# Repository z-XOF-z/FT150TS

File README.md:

<div align="center">

<br/>

**El tablero que la FT150TS no traía de fábrica.**

Tablero digital + launcher para Android que funciona **solo con el teléfono** del manubrio
y está listo para una tarjeta **ESP32** en la moto.

[![Android][android-shield]](#empezar)
[![Kotlin][kotlin-shield]](app/src/main/java/com/xof/ft150ts)
[![Jetpack Compose][compose-shield]](app/src/main/java/com/xof/ft150ts/ui)
[![ESP32-S3][esp32-shield]](firmware/ft150ts_dashboard)
[![Versión][version-shield]](LEEME.md)

### [⬇ Descargar la app (APK v3.4 estable)](https://github.com/z-XOF-z/FT150TS/releases/latest)

**[Qué hace](#qué-hace)** · **[Empezar](#empezar)** · **[La tarjeta ESP32](#la-tarjeta-esp32)** · **[Historial completo](LEEME.md)**

</div>

---

## Por qué

El teléfono ya iba en el manubrio de la moto. En vez de solo mirar el mapa, se vuelve el **tablero completo**:
velocidad, RPM, marcha, inclinación, mantenimiento, gasolina y navegación, con un diseño pixel y deportivo
pensado para la FT150TS. Sin cables extra: las RPM salen de la **vibración del motor** que siente el teléfono.
Cuando llegue la tarjeta ESP32, ella manda los datos que el teléfono no puede medir (voltaje, temperatura, RPM
directas) y la app se cambia sola.

## Qué hace

<div align="center">

</div>

| Capacidad | Qué te da |
| --- | --- |
| **Tablero LCD Sport** | Barra de RPM curva o diagonal a 45°, dígitos de 7 segmentos, marcha, shift light y animación de arranque (las RPM suben al tope y regresan, como al dar switch). |
| **RPM sin sensor** | La vibración del motor por FFT de 3 ejes, peine de armónicos y filtro de Kalman. Se calibra en 6 s en ralentí. |
| **Marcha** | Velocidad + RPM + la marcha anterior en un filtro de probabilidad: no marca "4ª a 17 km/h". |
| **Aguja con PID** | La aguja tiene inercia de verdad; Kp, Ki y Kd ajustables con gráfica de respuesta. |
| **Mapa** | OpenStreetMap que gira suave con la brújula, satélites y doble frecuencia L5, dónde dejé la moto, límite de velocidad, "llévame a casa". |
| **Modo moto** | El cable de la moto hace de switch: carga = tablero, sin carga = tus apps. Etiqueta NFC del soporte y **modo sueño** cuando carga sin moverse. |
| **Launcher** | Pantalla de inicio con tus apps, 4 accesos directos y tres estilos de íconos (normales, pixel, LCD). |
| **Rodadas** | Cada rodada se graba sola; mírala en el mapa pintado por velocidad y **repítela** x10/x30/x60. Aviso de descanso. |
| **Arrancones** | 0-40/60/80, 100 m y 1/8 de milla con semáforo y tiempo de reacción, y prueba de frenado 40→0 (en lugar cerrado). |
| **Lluvia en tu ruta** | Revisa el pronóstico kilómetros adelante en la dirección en que vas y te avisa antes de mojarte. |
| **Velocímetro vs GPS** | Cuánto marca de más tu velocímetro y a cuánto vas de verdad. |
| **Mantenimiento** | Odómetro del teléfono, servicios por km, bitácora de gasolina con rendimiento y **alcance**. |
| **Respaldo** | Todos tus datos en un archivo: guárdalo, compártelo o deja el automático semanal. |
| **Seguridad** | Dashcam en bucle que guarda el video si detecta un golpe, aviso de teléfono caliente, batería del cel. |
| **Clima y alertas** | Lluvia próxima, huracanes (NHC), sismos (USGS) y clima severo en el tablero. |
| **Temas** | **Vértice** (riel lateral, nuevo), Carbono, Vidrio, Filo, Pixel, Táctico, Holo, Ácido y Circuito · efecto neón · 18 colores + uno personalizado · 4 fondos. |
| **Reposo** | Moto parada y cargando: reloj atenuado o pantalla apagada, GPS en pausa; despierta solo al dar marcha. |

### La idea en una línea

> El teléfono que ya va en el manubrio se vuelve el tablero; la ESP32 le da lo que el teléfono no puede medir.

## Empezar

### 1. Instala la app

**La rápida:** descarga el APK del [último release](https://github.com/z-XOF-z/FT150TS/releases/latest) en tu
teléfono (Android 8.0 o más nuevo), ábrelo y permite "Instalar apps desconocidas".

**Actualizar:** desde la 3.2-beta.1, en la app: Ajustes → Acerca de → **Buscar actualización** (prende "Versiones de prueba" para recibir betas). Se instala encima sin
borrar tus datos. Detalles y cómo publicar una versión en [docs/RELEASE.md](docs/RELEASE.md).

**Desde el código:**

Abre esta carpeta en **Android Studio**, conecta el teléfono (depuración USB) y:

```bash
./gradlew installDebug      # normal
./gradlew installRelease    # optimizada, más fluida (misma firma: no borra tus datos)
```

Requiere Android 8.0 o más nuevo. Siempre se instala **encima**: tu odómetro, marchas aprendidas y ajustes se quedan.

### 2. Calibra las RPM (una vez)

Moto en neutral, motor caliente en ralentí y el teléfono en el soporte:
**Ajustes > Sin la tarjeta > Calibrar en ralentí** (6 segundos).

### 3. Escoge tu estilo

**Ajustes > Apariencia**: tema, color de acento, neón, fondo, forma de la barra de RPM y la animación de entrada.

## La tarjeta ESP32

Firmware en [`firmware/ft150ts_dashboard`](firmware/ft150ts_dashboard), placa **ESP32-S3**, particiones *Huge APP*:

```bash
arduino-cli compile --fqbn espressif:esp32:esp32s3:PartitionScheme=huge_app firmware/ft150ts_dashboard
```

Desde la v1.4 cada tarjeta genera su propia clave de WiFi (se ve por USB al encender o con `wifi clave`) y los
comandos delicados solo se aceptan de un teléfono vinculado. Detalles en [SEGURIDAD.md](SEGURIDAD.md).

## Placa base y piezas 3D

- **Placa base v2.3** para el ESP32-S3 N16R8 (10×10 cm, 2 capas, piezas de agujero de tiendas de México): guía de armado y conexiones a la moto en [`pcb/ARMADO.md`](pcb/ARMADO.md), esquemático en [PDF](pcb/esquematico/ft150ts_B_esquema.pdf), gerbers para JLCPCB en [`pcb/fabricar/B_JLCPCB`](pcb/fabricar/B_JLCPCB) y piezas en [`pcb/LISTA_COMPRAS.md`](pcb/LISTA_COMPRAS.md).
- **Placas extra** (expansión I2C con 3 relevadores, fusibles y perforada): [`pcb/extras`](pcb/extras).
- **Simulaciones** de cada bloque (ngspice/KiCad): [`pcb/simulacion`](pcb/simulacion).
- **Piezas 3D** (CadQuery): soporte del teléfono para el manubrio y caja de la placa bajo el asiento, en [`carcasa`](carcasa) (STL y STEP).
- Mapa de todo el proyecto: [`docs/MAPA.md`](docs/MAPA.md).

## Temas

<div align="center">

<br/><sub>Tema Filo: barra integrada con segmentos a 45° y todo dentro de un marco tipo visor.</sub>
</div>

## Hoja de ruta

- [x] Tablero LCD Sport y Clásico con aguja PID
- [x] RPM por vibración, marcha por velocidad + RPM
- [x] Modo moto, NFC, modo sueño
- [x] Temas Filo, Pixel y Táctico, neón y colores personalizados
- [x] Respaldo y restaurar todos tus datos en un archivo
- [x] Modo arrancones (0–60 km/h, 1/8 de milla, semáforo) y prueba de frenado
- [x] Lluvia en tu ruta
- [x] Repetición de rodadas coloreada por velocidad
- [x] Error del velocímetro contra el GPS
- [x] Logros pixel (y un secreto)
- [x] Tema Vértice, modo reposo y medidor de fluidez
- [x] Auditoría de seguridad (WiFi y Bluetooth de la tarjeta, respaldo)
- [ ] Antirrobo (con la ESP32)
- [ ] Temperatura del motor, nivel de gasolina real y presión de llantas (con la ESP32)

## Estructura

```
app/                      App de Android (Kotlin + Jetpack Compose)
  src/main/java/com/xof/ft150ts/
    ui/                   Pantallas, temas, barra integrada, animaciones
    *.kt                  GPS, sensores, RPM, marcha, modo moto, modo sueño...
firmware/
  ft150ts_dashboard/      Firmware del ESP32-S3 (Arduino)
docs/                     Banner animado, GIFs e imágenes
releases/                 APK listo para instalar y notas de cada versión
LEEME.md                  Guía completa e historial de versiones
```

---

<div align="center">

Hecho por **XOF** para su Italika FT150TS.

<sub>Tipografías Chakra Petch, Russo One y Press Start 2P con licencia OFL ([LICENCIAS_FUENTES.txt](LICENCIAS_FUENTES.txt)) · Mapas © colaboradores de OpenStreetMap</sub>

</div>

[android-shield]: https://img.shields.io/badge/Android-8.0%2B-9BE22B?style=for-the-badge&logo=android&logoColor=white&labelColor=0E1113
[kotlin-shield]: https://img.shields.io/badge/Kotlin-2.1-9BE22B?style=for-the-badge&logo=kotlin&logoColor=white&labelColor=0E1113
[compose-shield]: https://img.shields.io/badge/Jetpack%20Compose-Material%203-9BE22B?style=for-the-badge&logo=jetpackcompose&logoColor=white&labelColor=0E1113
[esp32-shield]: https://img.shields.io/badge/ESP32--S3-firmware-9BE22B?style=for-the-badge&logo=espressif&logoColor=white&labelColor=0E1113
[version-shield]: https://img.shields.io/badge/versi%C3%B3n-3.4-9BE22B?style=for-the-badge&labelColor=0E1113

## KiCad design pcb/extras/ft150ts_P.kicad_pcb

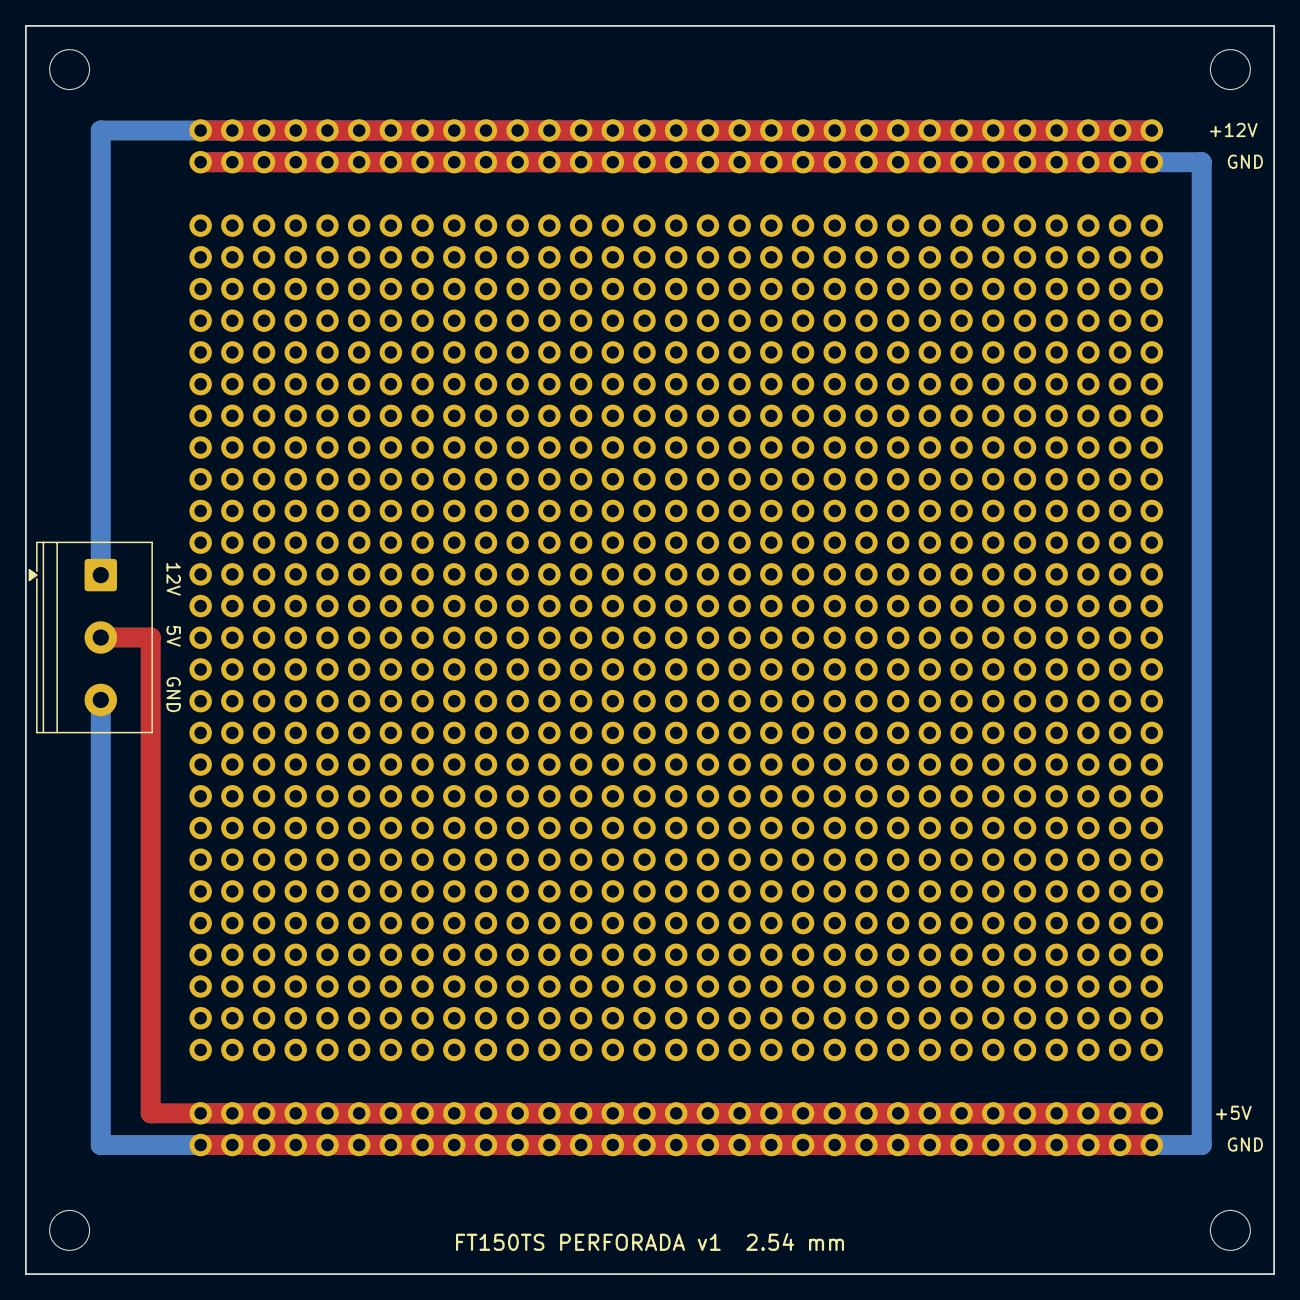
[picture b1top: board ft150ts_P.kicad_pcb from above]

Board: 2 copper layers, 100.0 x 100.0 mm, 6 parts (0 on the bottom side), 3 nets.

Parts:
H1, H2, H3, H4: MountingHole_3.2mm_M3
J1: TerminalBlock_Phoenix_PT-1,5-3-5.0-H_1x03_P5.00mm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; TerminalBlock_Phoenix_PT-1,5-3-5.0-H_1x03_P5.00mm_Horizontal
PERF: (no value)

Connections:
+5V: J1.2, PERF.30, PERF.61, PERF.92, PERF.123, PERF.154, PERF.185, PERF.216, PERF.247, PERF.278, PERF.309, PERF.340, PERF.371, PERF.402, PERF.433, PERF.464, PERF.495, PERF.526, PERF.557, PERF.588, PERF.619, PERF.650, PERF.681, PERF.712, PERF.743, PERF.774, PERF.805, PERF.836, PERF.867, PERF.898, PERF.929, PERF.960
+12V: J1.1, PERF.28, PERF.59, PERF.90, PERF.121, PERF.152, PERF.183, PERF.214, PERF.245, PERF.276, PERF.307, PERF.338, PERF.369, PERF.400, PERF.431, PERF.462, PERF.493, PERF.524, PERF.555, PERF.586, PERF.617, PERF.648, PERF.679, PERF.710, PERF.741, PERF.772, PERF.803, PERF.834, PERF.865, PERF.896, PERF.927, PERF.958
GND: J1.3, PERF.29, PERF.31, PERF.60, PERF.62, PERF.91, PERF.93, PERF.122, PERF.124, PERF.153, PERF.155, PERF.184, PERF.186, PERF.215, PERF.217, PERF.246, PERF.248, PERF.277, PERF.279, PERF.308, PERF.310, PERF.339, PERF.341, PERF.370, PERF.372, PERF.401, PERF.403, PERF.432, PERF.434, PERF.463, PERF.465, PERF.494, PERF.496, PERF.525, PERF.527, PERF.556, PERF.558, PERF.587, PERF.589, PERF.618, PERF.620, PERF.649, PERF.651, PERF.680, PERF.682, PERF.711, PERF.713, PERF.742, PERF.744, PERF.773, PERF.775, PERF.804, PERF.806, PERF.835, PERF.837, PERF.866, PERF.868, PERF.897, PERF.899, PERF.928, PERF.930, PERF.959, PERF.961

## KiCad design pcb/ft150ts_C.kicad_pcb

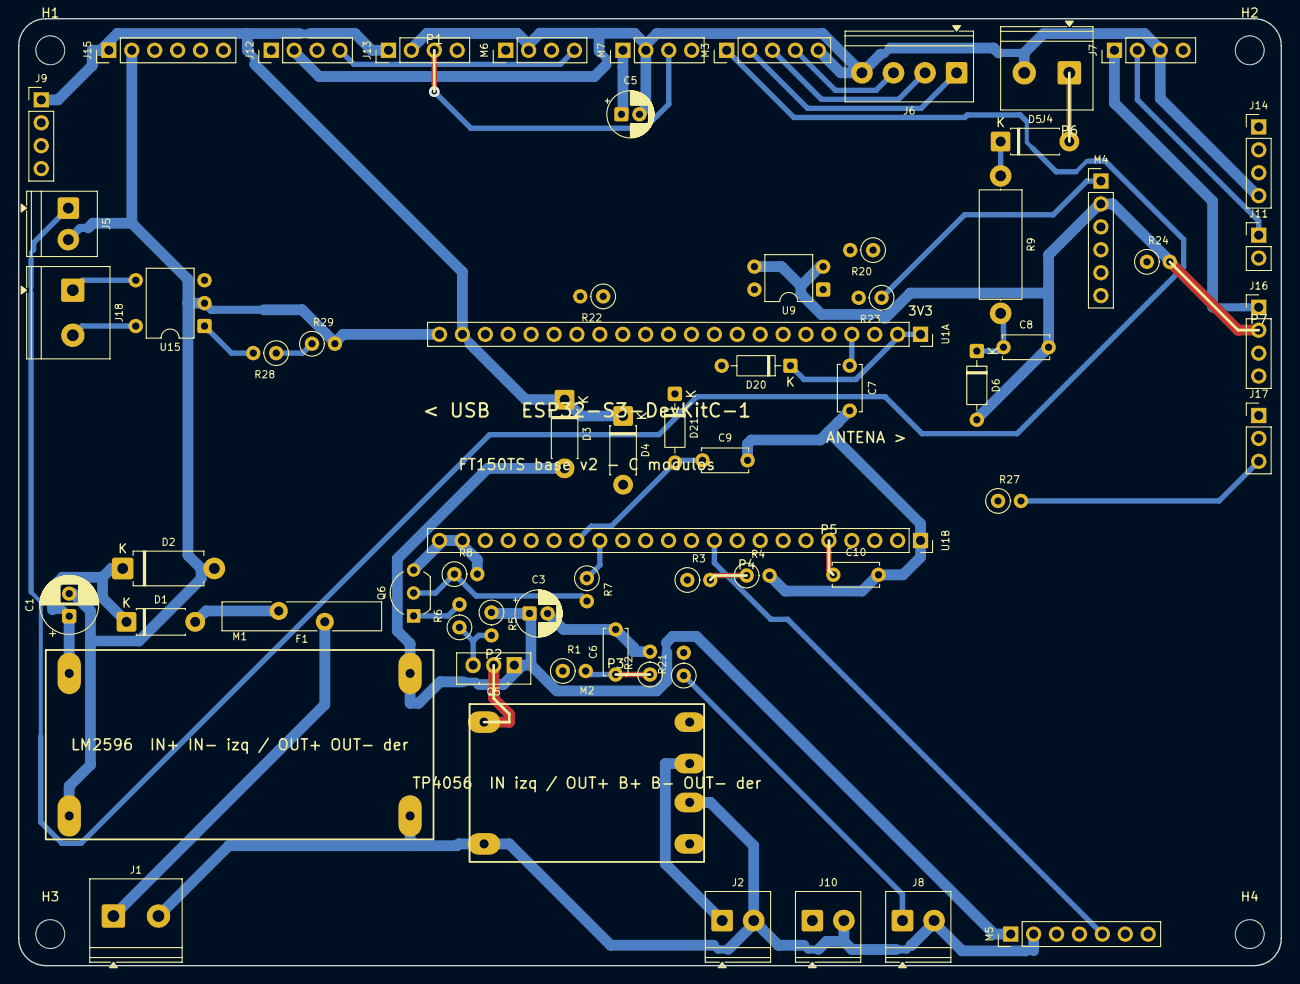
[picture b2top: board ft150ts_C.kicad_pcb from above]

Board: 2 copper layers, 140.0 x 105.0 mm, 68 parts (0 on the bottom side), 57 nets.

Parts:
C1: 100uF 35V; CP_Radial_D6.3mm_P2.50mm
C3, C5: 100uF 10V; CP_Radial_D5.0mm_P2.00mm
C6, C7, C9, C10: 100nF; C_Disc_D5.0mm_W2.5mm_P5.00mm
C8: 4.7nF; C_Disc_D5.0mm_W2.5mm_P5.00mm
D1, D3, D4: 1N5819; D_DO-41_SOD81_P7.62mm_Horizontal
D2: P6KE22A; D_DO-15_P10.16mm_Horizontal
D5: 1N4007; D_DO-41_SOD81_P7.62mm_Horizontal
D6: 1N4148; D_DO-35_SOD27_P7.62mm_Horizontal
D20, D21: BAT85; D_DO-35_SOD27_P7.62mm_Horizontal
F1: MF-R110 1.1A; Fuse_Bourns_MF-RG1100
H1, H2, H3, H4: MountingHole_3.2mm_M3
J1: BAT MOTO 12V; TerminalBlock_Phoenix_PT-1,5-2-5.0-H_1x02_P5.00mm_Horizontal
J2: BATERIA 3.7V; TerminalBlock_Phoenix_PT-1,5-2-3.5-H_1x02_P3.50mm_Horizontal
J4: BOBINA; TerminalBlock_Phoenix_PT-1,5-2-5.0-H_1x02_P5.00mm_Horizontal
J5: LLAVE; TerminalBlock_Phoenix_PT-1,5-2-3.5-H_1x02_P3.50mm_Horizontal
J6: ENTRADAS 3-16V; TerminalBlock_Phoenix_PT-1,5-4-3.5-H_1x04_P3.50mm_Horizontal
J7: HALL; PinHeader_1x04_P2.54mm_Vertical
J8: QUICKSHIFT; TerminalBlock_Phoenix_PT-1,5-2-3.5-H_1x02_P3.50mm_Horizontal
J9: DS18B20; PinHeader_1x04_P2.54mm_Vertical
J10: GASOLINA; TerminalBlock_Phoenix_PT-1,5-2-3.5-H_1x02_P3.50mm_Horizontal
J11: LDR; PinHeader_1x02_P2.54mm_Vertical
J12: I2C 3V3; PinHeader_1x04_P2.54mm_Vertical
J13: LCD 5V; PinHeader_1x04_P2.54mm_Vertical
J14: BOTONES; PinHeader_1x04_P2.54mm_Vertical
J15: SD; PinHeader_1x06_P2.54mm_Vertical
J16: GPS; PinHeader_1x04_P2.54mm_Vertical
J17: LEDS; PinHeader_1x03_P2.54mm_Vertical
J18: CDI PARO; TerminalBlock_Phoenix_PT-1,5-2-5.0-H_1x02_P5.00mm_Horizontal
M1: LM2596; Modulo_LM2596_43x21
M2: TP4056; Modulo_TP4056_26x17
M3: OPTO 4CH ENTRADA; PinHeader_1x05_P2.54mm_Vertical
M4: OPTO 4CH SALIDA; PinHeader_1x06_P2.54mm_Vertical
M5: RELES 4CH; PinHeader_1x07_P2.54mm_Vertical
M6: NIVEL LV; PinHeader_1x04_P2.54mm_Vertical
M7: NIVEL HV; PinHeader_1x04_P2.54mm_Vertical
Q5: BD140; TO-126-3_Vertical
Q6: BC547; TO-92_Inline_Wide
R1, R3, R4: 100k; R_Axial_DIN0207_L6.3mm_D2.5mm_P2.54mm_Vertical
R2: 22k; R_Axial_DIN0207_L6.3mm_D2.5mm_P2.54mm_Vertical
R5, R7, R23: 1k; R_Axial_DIN0207_L6.3mm_D2.5mm_P2.54mm_Vertical
R6: 150; R_Axial_DIN0207_L6.3mm_D2.5mm_P2.54mm_Vertical
R8, R24, R29: 10k; R_Axial_DIN0207_L6.3mm_D2.5mm_P2.54mm_Vertical
R9: 47k 1W; R_Axial_DIN0414_L11.9mm_D4.5mm_P15.24mm_Horizontal
R20, R21: 2.2k; R_Axial_DIN0207_L6.3mm_D2.5mm_P2.54mm_Vertical
R22: 4.7k; R_Axial_DIN0207_L6.3mm_D2.5mm_P2.54mm_Vertical
R27, R28: 330; R_Axial_DIN0207_L6.3mm_D2.5mm_P2.54mm_Vertical
U1A: DevKitC-1 J1; PinSocket_1x22_P2.54mm_Vertical
U1B: DevKitC-1 J3; PinSocket_1x22_P2.54mm_Vertical
U9: PC817; DIP-4_W7.62mm
U15: PhotoMOS 600V; DIP-6_W7.62mm_SinPin5

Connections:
+3V3: D20.1, D21.1, J7.2, J9.2, J11.1, J12.1, M4.1, M5.3, M6.1, R22.1, R23.1, U1A.1, U1A.2
+5V: C5.1, D3.1, D4.1, J7.1, J9.1, J13.1, J15.1, J16.1, J17.1, M7.1, U1A.21
+5V_MOTO: C3.1, D3.2, M1.3, M5.1, Q5.1, R5.1
+12V: C1.1, D1.1, D2.1, M1.1
+12V_F: D1.2, F1.2
+12V_IN: F1.1, J1.1, R1.1
BOBINA: D5.2, J4.1
CARGA5: M2.1, Q5.2
CARGA_B: Q6.2, R7.2, R8.1
CARGA_BP: Q5.3, R5.2, R6.1
CARGA_C: Q6.1, R6.2
CDI_PARO: J18.1, U15.4
CDI_TIERRA: J18.2, U15.6
CELDA: D4.2, J2.1, M2.3, R3.1
ENT1: J6.1, M3.2
ENT2: J6.2, M3.3
ENT3: J6.3, M3.4
GND: C1.2, C3.2, C5.2, C6.2, C7.2, C8.2, C9.2, C10.2, D2.2, D6.2, J1.2, J2.2, J4.2, J5.2, J6.4, J7.3, J8.2, J9.3, J10.2, J12.2, J13.2, J14.4, J15.2, J16.2, J17.2, M1.2, M1.4, M2.2, M2.4, M3.5, M4.2, M5.2, M6.2, M7.2, Q6.3, R2.2, R4.2, R8.2, R24.2, R29.2, U1A.22, U1B.1, U1B.21, U1B.22, U9.2, U9.3, U15.2
IO1: C6.1, R1.2, R2.1, U1B.4
IO2: C10.1, J10.1, R23.2, U1B.5
IO3: M4.5, U1A.13
IO4: C7.1, R3.2, R4.1, U1A.4
IO5: J11.2, R24.1, U1A.5
IO6: J14.1, U1A.6
IO7: J14.2, U1A.7
IO8: J12.3, M6.3, U1A.12
IO9: J12.4, M6.4, U1A.15
IO10: J15.3, U1A.16
IO11: J15.4, U1A.17
IO12: J15.5, U1A.18
IO13: J15.6, U1A.19
IO14: J9.4, R22.2, U1A.20
IO15: J14.3, U1A.8
IO16: U1A.9, U9.4
IO17: D20.2, R20.2, U1A.10
IO18: M4.4, U1A.11
IO21: M4.3, U1B.18
IO38: M5.5, U1B.10
IO39: R27.1, U1B.9
IO40: M5.4, U1B.8
IO41: J16.3, U1B.7
IO42: J16.4, U1B.6
IO43: M5.7, U1B.2
IO44: M5.6, U1B.3
IO45: R7.1, U1B.15
IO46: M4.6, U1A.14
IO47: R28.1, R29.1, U1B.17
IO48: C9.1, D21.2, R21.2, U1B.16
LED_DIN: J17.3, R27.2
LLAVE: J5.1, M3.1
OPT9_A: C8.1, D6.1, R9.2, U9.1
RPM_A: D5.1, R9.1
S20: J7.4, R20.1
S21: J8.1, R21.1
SCL5: J13.4, M7.4
SDA5: J13.3, M7.3
SSR_A: R28.2, U15.1

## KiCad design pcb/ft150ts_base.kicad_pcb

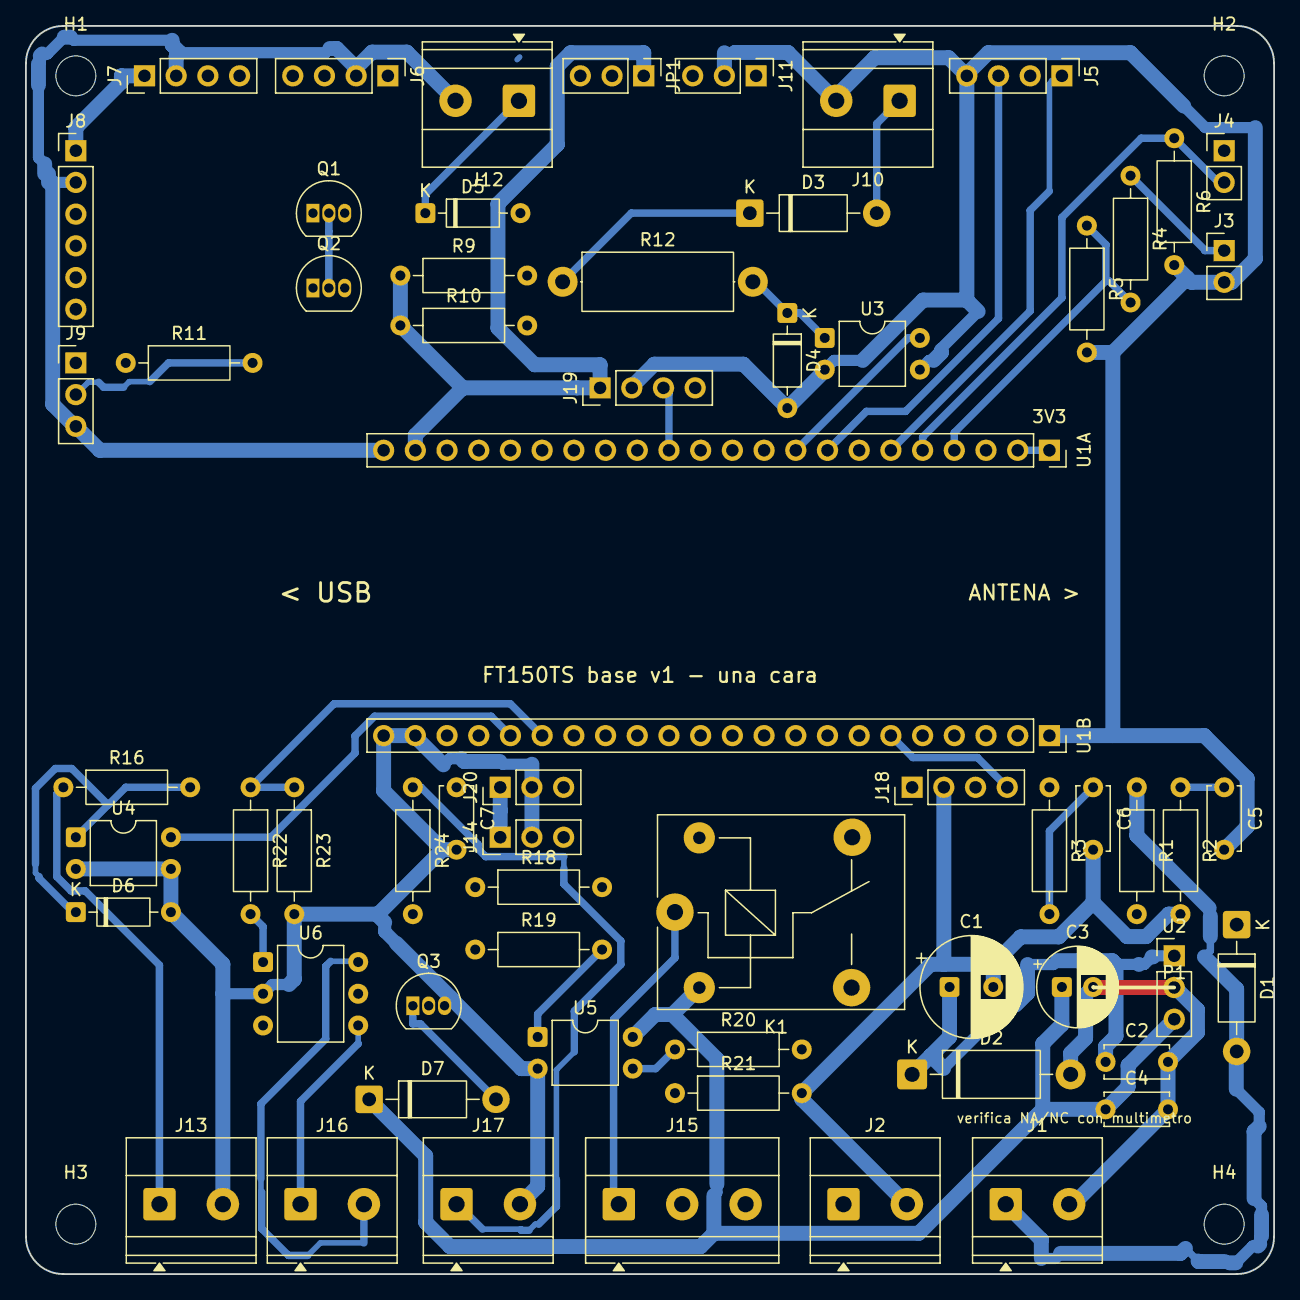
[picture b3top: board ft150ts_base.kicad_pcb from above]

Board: 2 copper layers, 100.0 x 100.0 mm, 68 parts (0 on the bottom side), 54 nets.

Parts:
C1: 100uF 35V; CP_Radial_D8.0mm_P3.50mm
C2, C4, C5, C6, C7: 100nF; C_Disc_D5.0mm_W2.5mm_P5.00mm
C3: 100uF 10V; CP_Radial_D6.3mm_P2.50mm
D1: 1N5819; D_DO-41_SOD81_P10.16mm_Horizontal
D2: P6KE24A; D_DO-15_P12.70mm_Horizontal
D3, D7: 1N4007; D_DO-41_SOD81_P10.16mm_Horizontal
D4, D5, D6: 1N4148; D_DO-35_SOD27_P7.62mm_Horizontal
H1, H2, H3, H4: MountingHole_3.2mm_M3
J1: 12V MOTO; TerminalBlock_Phoenix_MKDS-1,5-2-5.08_1x02_P5.08mm_Horizont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
J2: GASOLINA; TerminalBlock_Phoenix_MKDS-1,5-2-5.08_1x02_P5.08mm_Horizont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
J3: 18650; PinHeader_1x02_P2.54mm_Vertical
J4: LDR; PinHeader_1x02_P2.54mm_Vertical
J5: BOTONES; PinHeader_1x04_P2.54mm_Vertical
J6: I2C 3V3; PinHeader_1x04_P2.54mm_Vertical
J7: LCD 5V; PinHeader_1x04_P2.54mm_Vertical
J8: SD; PinHeader_1x06_P2.54mm_Vertical
J9: DS18B20; PinHeader_1x03_P2.54mm_Vertical
J10: BOBINA; TerminalBlock_Phoenix_MKDS-1,5-2-5.08_1x02_P5.08mm_Horizont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
J11: HALL; PinHeader_1x03_P2.54mm_Vertical
J12: NEUTRAL; TerminalBlock_Phoenix_MKDS-1,5-2-5.08_1x02_P5.08mm_Horizont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
J13: LLAVE; TerminalBlock_Phoenix_MKDS-1,5-2-5.08_1x02_P5.08mm_Horizont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
J14: LEDS; PinHeader_1x03_P2.54mm_Vertical
J15: RELE; TerminalBlock_Phoenix_MKDS-1,5-3-5.08_1x03_P5.08mm_Horizont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
J16: CDI PARO; TerminalBlock_Phoenix_MKDS-1,5-2-5.08_1x02_P5.08mm_Horizont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
J17: QUICKSHIFT; TerminalBlock_Phoenix_MKDS-1,5-2-5.08_1x02_P5.08mm_Horizont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
J18: GPS; PinHeader_1x04_P2.54mm_Vertical
J19: RELES EXTRA; PinHeader_1x04_P2.54mm_Vertical
J20: RELE EXTRA 3; PinHeader_1x03_P2.54mm_Vertical
JP1: VSENS 5V|3V3; PinHeader_1x03_P2.54mm_Vertical
K1: SRD-05VDC-SL-C; Relay_SPDT_SANYOU_SRD_Series_Form_C
Q1, Q2: 2N7000; TO-92_Inline
Q3: BC547; TO-92_Inline
R1, R4, R5: 100k; R_Axial_DIN0207_L6.3mm_D2.5mm_P10.16mm_Horizontal
R2: 22k; R_Axial_DIN0207_L6.3mm_D2.5mm_P10.16mm_Horizontal
R3, R19, R20, R24: 1k; R_Axial_DIN0207_L6.3mm_D2.5mm_P10.16mm_Horizontal
R6, R9, R10, R21, R23: 10k; R_Axial_DIN0207_L6.3mm_D2.5mm_P10.16mm_Horizontal
R11: 4.7k; R_Axial_DIN0207_L6.3mm_D2.5mm_P10.16mm_Horizontal
R12: 47k 1W; R_Axial_DIN0414_L11.9mm_D4.5mm_P15.24mm_Horizontal
R16: 2.2k; R_Axial_DIN0207_L6.3mm_D2.5mm_P10.16mm_Horizontal
R18, R22: 330; R_Axial_DIN0207_L6.3mm_D2.5mm_P10.16mm_Horizontal
U1A: DevKitC-1 J1; PinSocket_1x22_P2.54mm_Vertical
U1B: DevKitC-1 J3; PinSocket_1x22_P2.54mm_Vertical
U2: R-78E5.0-1.0; PinHeader_1x03_P2.54mm_Vertical
U3, U4, U5: PC817; DIP-4_W7.62mm
U6: PhotoMOS 600V; DIP-6_W7.62mm

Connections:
+3V3: J4.1, J6.1, JP1.3, Q1.2, Q2.2, R3.1, R11.1, U1A.1, U1A.2
+5V: C3.1, C4.1, D7.1, J7.1, J8.1, J14.1, J18.1, J19.1, J20.1, JP1.1, K1.2, R9.1, R10.1, U1A.21, U2.3, U5.4
+12V: C1.1, C2.1, D1.1, D2.1, U2.1
+12V_IN: D1.2, J1.1, R1.1
BOBINA: D3.2, J10.1
CDI_PARO: J16.1, U6.4
CDI_TIERRA: J16.2, U6.6
GND: C1.2, C2.2, C3.2, C4.2, C5.2, C6.2, C7.2, D2.2, D4.2, D6.2, J1.2, J2.2, J3.2, J5.4, J6.2, J7.2, J8.2, J9.3, J10.2, J11.2, J12.2, J13.2, J14.2, J17.2, J18.2, J19.2, J20.2, Q3.3, R2.2, R5.2, R6.2, R21.2, R23.2, U1A.22, U1B.1, U1B.21, U1B.22, U2.2, U3.2, U3.3, U4.2, U4.3, U5.2, U6.2
IO1: C5.1, R1.2, R2.1, U1B.4
IO2: C6.1, J2.1, R3.2, U1B.5
IO3: J19.3, U1A.13
IO4: R4.2, R5.1, U1A.4
IO5: J4.2, R6.1, U1A.5
IO6: J5.1, U1A.6
IO7: J5.2, U1A.7
IO8: J6.3, Q1.1, U1A.12
IO9: J6.4, Q2.1, U1A.15
IO10: J8.3, U1A.16
IO11: J8.4, U1A.17
IO12: J8.5, U1A.18
IO13: J8.6, U1A.19
IO14: J9.2, R11.2, U1A.20
IO15: J5.3, U1A.8
IO16: U1A.9, U3.4
IO17: J11.3, U1A.10
IO18: D5.2, U1A.11
IO21: U1B.18, U4.4
IO38: J20.3, U1B.10
IO39: R18.1, U1B.9
IO40: R19.1, U1B.8
IO41: J18.3, U1B.7
IO42: J18.4, U1B.6
IO46: J19.4, U1A.14
IO47: R22.1, R23.1, U1B.17
IO48: C7.1, R24.2, U1B.16
LED_DIN: J14.3, R18.2
LIPO: J3.1, R4.1
LLAVE: J13.1, R16.1
NEUTRAL: D5.1, J12.1
OPT1_A: D4.1, R12.2, U3.1
OPT2_A: D6.1, R16.2, U4.1
OPT3_A: R19.2, U5.1
QS: J17.1, R24.1
RLY_B: Q3.2, R20.2, R21.1
RLY_BOB: D7.2, K1.5, Q3.1
RLY_COM: J15.1, K1.1
RLY_E: R20.1, U5.3
RLY_NA: J15.2, K1.4
RLY_NC: J15.3, K1.3
RPM_A: D3.1, R12.1
SCL5: J7.4, Q2.3, R10.2
SDA5: J7.3, Q1.3, R9.2
SSR_A: R22.2, U6.1
VSENS: J9.1, J11.1, JP1.2

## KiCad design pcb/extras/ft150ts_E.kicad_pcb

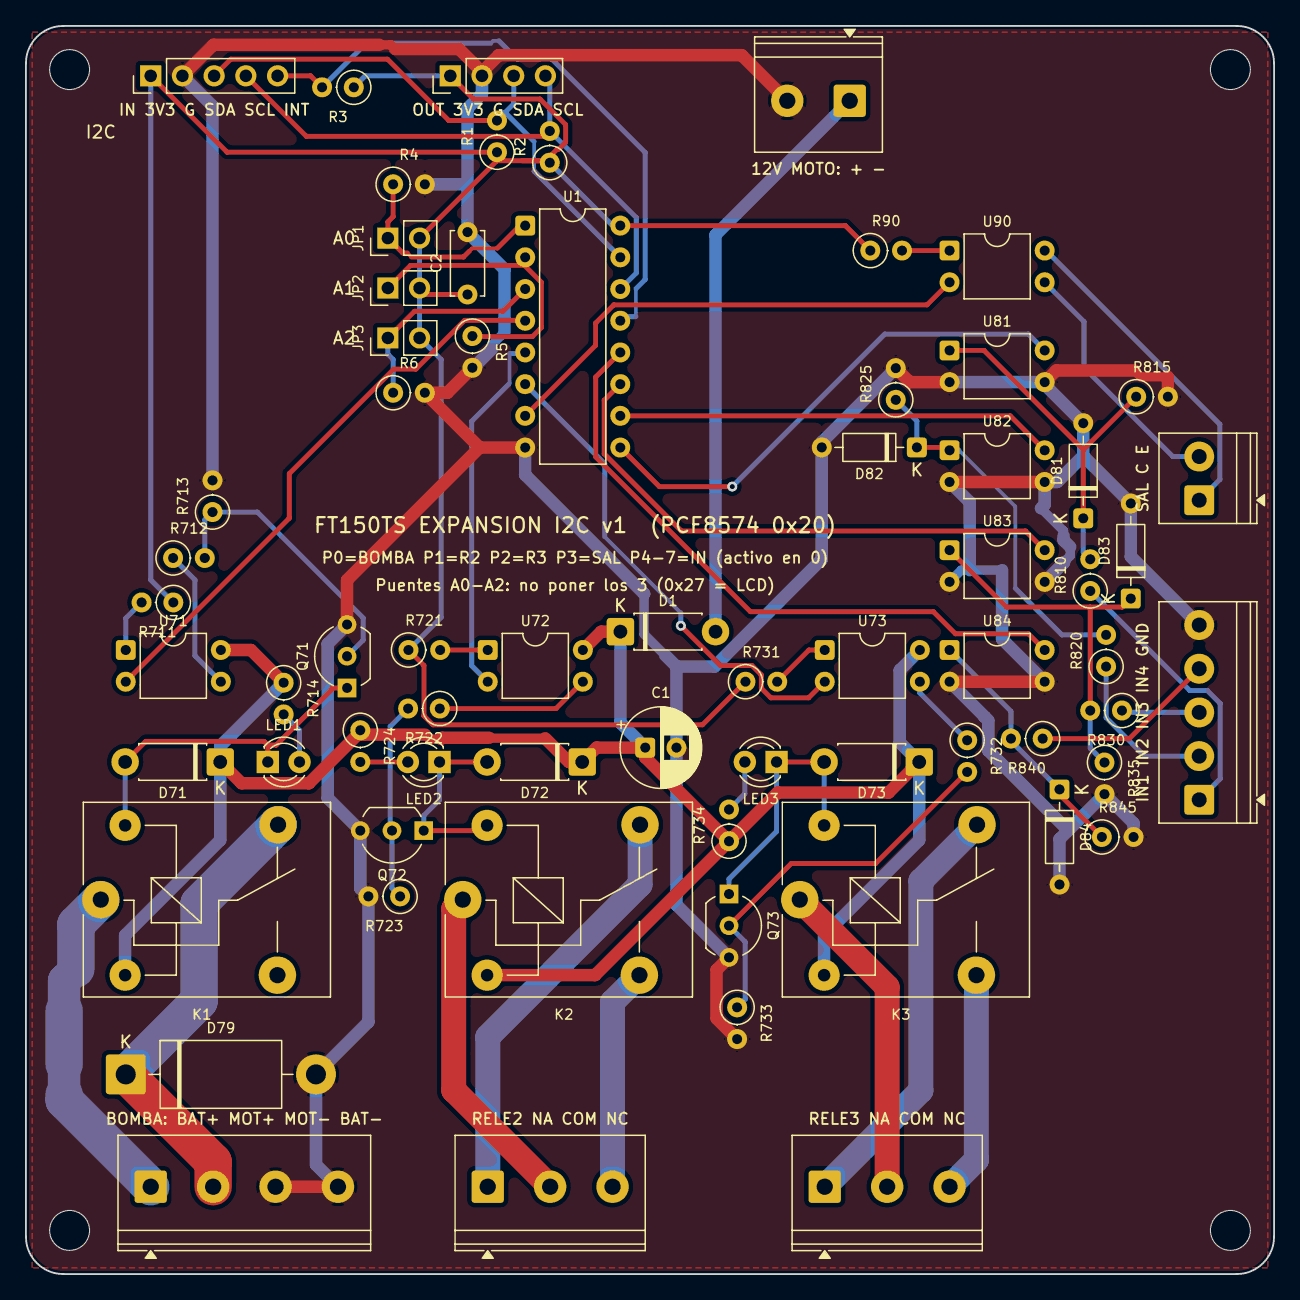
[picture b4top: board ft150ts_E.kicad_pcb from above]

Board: 2 copper layers, 100.0 x 100.0 mm, 71 parts (0 on the bottom side), 52 nets.

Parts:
C1: 100uF 25V; CP_Radial_D6.3mm_P2.50mm
C2: 100nF; C_Disc_D5.0mm_W2.5mm_P5.00mm
D1, D71, D72, D73: 1N4007; D_DO-41_SOD81_P7.62mm_Horizontal
D79: 1N5408; D_DO-201AD_P15.24mm_Horizontal
D81, D82, D83, D84: 1N4148; D_DO-35_SOD27_P7.62mm_Horizontal
H1, H2, H3, H4: MountingHole_3.2mm_M3
J1: I2C ENTRADA; PinHeader_1x05_P2.54mm_Vertical
J2: I2C SALIDA; PinHeader_1x04_P2.54mm_Vertical
J3: 12V; TerminalBlock_Phoenix_PT-1,5-2-5.0-H_1x02_P5.00mm_Horizontal
J71: BOMBA; TerminalBlock_Phoenix_PT-1,5-4-5.0-H_1x04_P5.00mm_Horizontal
J72: RELE 2; TerminalBlock_Phoenix_PT-1,5-3-5.0-H_1x03_P5.00mm_Horizontal
J73: RELE 3; TerminalBlock_Phoenix_PT-1,5-3-5.0-H_1x03_P5.00mm_Horizontal
J80: ENTRADAS; TerminalBlock_Phoenix_PT-1,5-5-3.5-H_1x05_P3.50mm_Horizontal
J90: SALIDA; TerminalBlock_Phoenix_PT-1,5-2-3.5-H_1x02_P3.50mm_Horizontal
JP1: A0; PinHeader_1x02_P2.54mm_Vertical
JP2: A1; PinHeader_1x02_P2.54mm_Vertical
JP3: A2; PinHeader_1x02_P2.54mm_Vertical
K1, K2, K3: SRD-12VDC-SL-C; Relay_SPDT_SANYOU_SRD_Series_Form_C
LED1, LED2, LED3: rojo; LED_D3.0mm
Q71, Q72, Q73: BC547; TO-92_Inline_Wide
R1, R2, R3, R4, R5, R6, R713, R723, R733: 10k; R_Axial_DIN0207_L6.3mm_D2.5mm_P2.54mm_Vertical
R90, R711, R721, R731: 330; R_Axial_DIN0207_L6.3mm_D2.5mm_P2.54mm_Vertical
R712, R722, R732: 1k; R_Axial_DIN0207_L6.3mm_D2.5mm_P2.54mm_Vertical
R714, R724, R734, R815, R825, R835, R845: 2.2k; R_Axial_DIN0207_L6.3mm_D2.5mm_P2.54mm_Vertical
R810, R820, R830, R840: 1.5k; R_Axial_DIN0207_L6.3mm_D2.5mm_P2.54mm_Vertical
U1: PCF8574P; DIP-16_W7.62mm
U71, U72, U73, U81, U82, U83, U84, U90: PC817; DIP-4_W7.62mm

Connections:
+3V3: C2.1, J1.1, J2.1, JP1.2, JP2.2, JP3.2, R1.1, R2.1, R3.1, R90.1, R711.1, R721.1, R731.1, U1.16
+12V: C1.1, D1.1, D71.1, D72.1, D73.1, K1.2, K2.2, K3.2, R714.1, R724.1, R734.1, U71.4, U72.4, U73.4
+12V_IN: D1.2, J3.1
A0: JP1.1, R4.1, U1.1
A1: JP2.1, R5.1, U1.2
A2: JP3.1, R6.1, U1.3
BOMBA_12V: J71.1, K1.1
GND: C1.2, C2.2, D79.2, D81.2, D82.2, D83.2, D84.2, J1.2, J2.2, J3.2, J71.3, J71.4, J80.5, Q71.3, Q72.3, Q73.3, R4.2, R5.2, R6.2, R713.2, R723.2, R733.2, R815.2, R825.2, R835.2, R845.2, U1.8, U81.2, U81.3, U82.2, U82.3, U83.2, U83.3, U84.2, U84.3
IN1: J80.1, R810.1
IN1_A: D81.1, R810.2, R815.1, U81.1
IN2: J80.2, R820.1
IN2_A: D82.1, R820.2, R825.1, U82.1
IN3: J80.3, R830.1
IN3_A: D83.1, R830.2, R835.1, U83.1
IN4: J80.4, R840.1
IN4_A: D84.1, R840.2, R845.1, U84.1
INT: J1.5, R3.2, U1.13
K1_BOB: D71.2, K1.5, LED1.1, Q71.1
K2_BOB: D72.2, K2.5, LED2.1, Q72.1
K2_COM: J72.2, K2.1
K2_NA: J72.1, K2.4
K2_NC: J72.3, K2.3
K3_BOB: D73.2, K3.5, LED3.1, Q73.1
K3_COM: J73.2, K3.1
K3_NA: J73.1, K3.4
K3_NC: J73.3, K3.3
LED1_A: LED1.2, R714.2
LED2_A: LED2.2, R724.2
LED3_A: LED3.2, R734.2
MOTOR_P: D79.1, J71.2, K1.4
P0: U1.4, U71.2
P1: U1.5, U72.2
P2: U1.6, U73.2
P3: U1.7, U90.2
P4: U1.9, U81.4
P5: U1.10, U82.4
P6: U1.11, U83.4
P7: U1.12, U84.4
RL1_A: R711.2, U71.1
RL1_B: Q71.2, R712.2, R713.1
RL1_E: R712.1, U71.3
RL2_A: R721.2, U72.1
RL2_B: Q72.2, R722.2, R723.1
RL2_E: R722.1, U72.3
RL3_A: R731.2, U73.1
RL3_B: Q73.2, R732.2, R733.1
RL3_E: R732.1, U73.3
SAL_A: R90.2, U90.1
SAL_C: J90.1, U90.4
SAL_E: J90.2, U90.3
SCL: J1.4, J2.4, R2.2, U1.14
SDA: J1.3, J2.3, R1.2, U1.15

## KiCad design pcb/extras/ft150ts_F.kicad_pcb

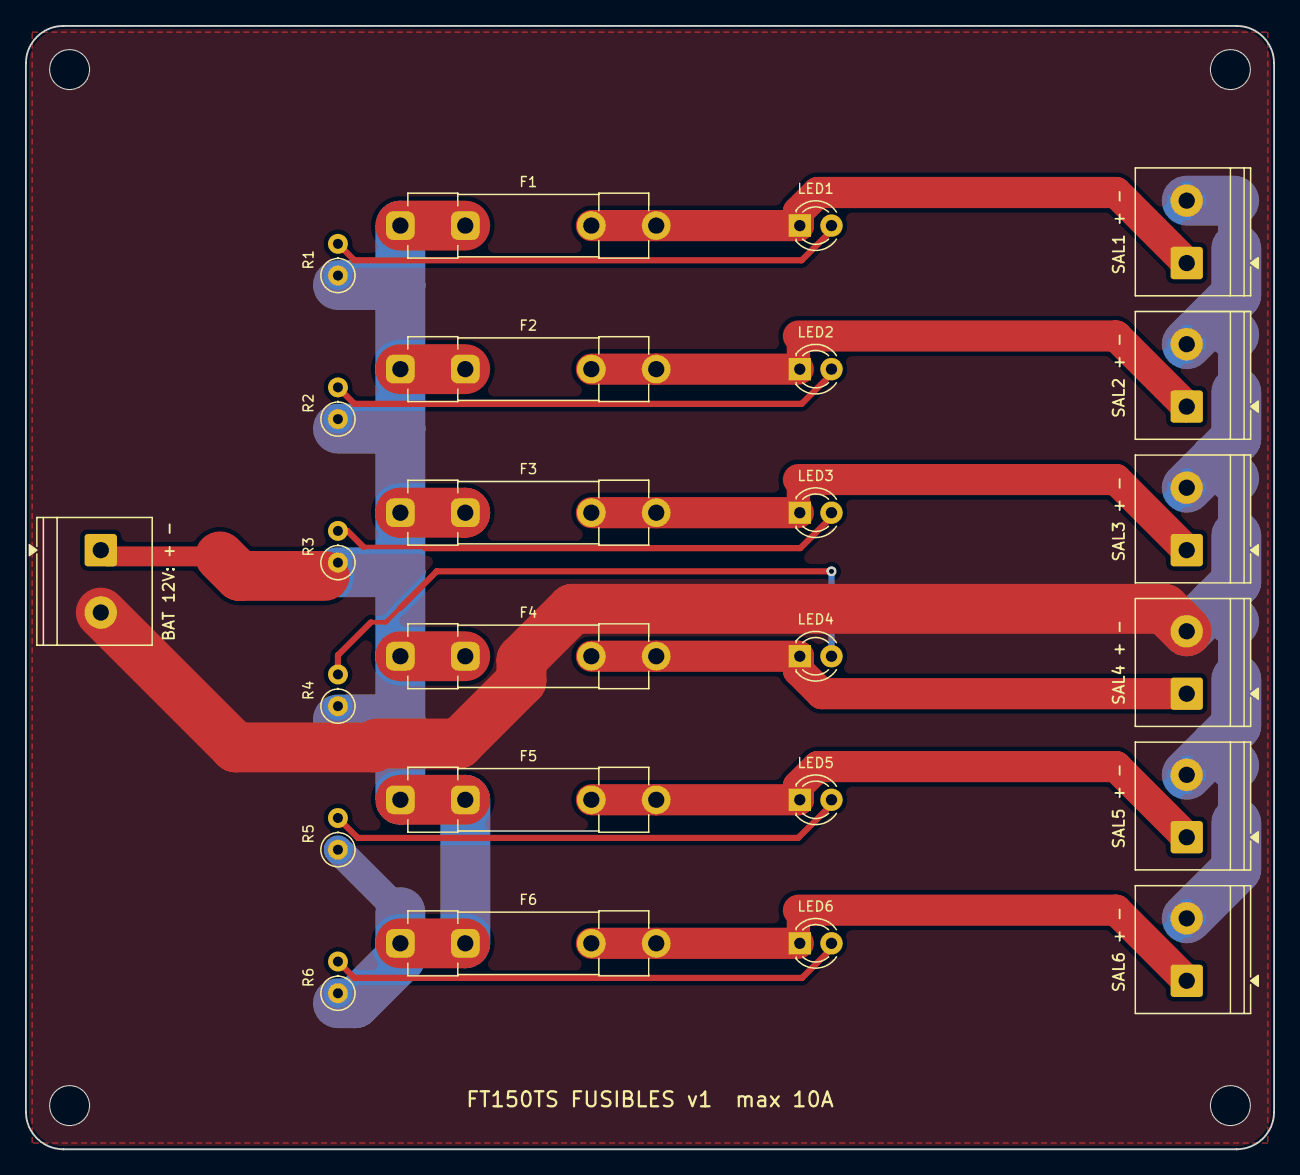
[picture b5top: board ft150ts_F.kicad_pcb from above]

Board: 2 copper layers, 100.0 x 90.0 mm, 29 parts (0 on the bottom side), 14 nets.

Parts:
F1, F2, F3, F4, F5, F6: 5x20; Fuseholder_Clip-5x20mm_Littelfuse_445-030_Inline_P20.50x5.2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
H1, H2, H3, H4: MountingHole_3.2mm_M3
J1: BATERIA 12V; TerminalBlock_Phoenix_PT-1,5-2-5.0-H_1x02_P5.00mm_Horizontal
J2: SALIDA 1; TerminalBlock_Phoenix_PT-1,5-2-5.0-H_1x02_P5.00mm_Horizontal
J3: SALIDA 2; TerminalBlock_Phoenix_PT-1,5-2-5.0-H_1x02_P5.00mm_Horizontal
J4: SALIDA 3; TerminalBlock_Phoenix_PT-1,5-2-5.0-H_1x02_P5.00mm_Horizontal
J5: SALIDA 4; TerminalBlock_Phoenix_PT-1,5-2-5.0-H_1x02_P5.00mm_Horizontal
J6: SALIDA 5; TerminalBlock_Phoenix_PT-1,5-2-5.0-H_1x02_P5.00mm_Horizontal
J7: SALIDA 6; TerminalBlock_Phoenix_PT-1,5-2-5.0-H_1x02_P5.00mm_Horizontal
LED1, LED2, LED3, LED4, LED5, LED6: rojo; LED_D3.0mm
R1, R2, R3, R4, R5, R6: 2.2k; R_Axial_DIN0207_L6.3mm_D2.5mm_P2.54mm_Vertical

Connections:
BUS12: F1.1, F2.1, F3.1, F4.1, F5.1, F6.1, J1.1, R1.1, R2.1, R3.1, R4.1, R5.1, R6.1
GND: J1.2, J2.2, J3.2, J4.2, J5.2, J6.2, J7.2
LED1_A: LED1.2, R1.2
LED2_A: LED2.2, R2.2
LED3_A: LED3.2, R3.2
LED4_A: LED4.2, R4.2
LED5_A: LED5.2, R5.2
LED6_A: LED6.2, R6.2
OUT1: F1.2, J2.1, LED1.1
OUT2: F2.2, J3.1, LED2.1
OUT3: F3.2, J4.1, LED3.1
OUT4: F4.2, J5.1, LED4.1
OUT5: F5.2, J6.1, LED5.1
OUT6: F6.2, J7.1, LED6.1

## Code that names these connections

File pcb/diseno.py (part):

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

def rele(n, k, gpio):
    """Relevador 5 V aislado: GPIO -> PC817 -> BC547 -> bobina. LED rojo = activado."""
    return [
        (f"R{n}1", F_R, "470", {1: gpio, 2: f"RL{k}_A"}),
        (f"U{n}", F_DIP4, "PC817", {1: f"RL{k}_A", 2: "GND", 3: f"RL{k}_E", 4: "+5V_MOTO"}),
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    ("R9", F_R_1W, "47k 1W", {1: "RPM_A", 2: "OPT9_A"}),
    ("D6", F_D35, "1N4148", {1: "OPT9_A", 2: "GND"}),
    ("C8", F_C, "4.7nF", {1: "OPT9_A", 2: "GND"}),
    ("U9", F_DIP4, "PC817", {1: "OPT9_A", 2: "GND", 3: "GND", 4: "IO16"}),

    # --- Entradas aisladas universales (3.3 a 16 V)
    ("J5", F_BORNE35(2), "LLAVE", {1: "LLAVE", 2: "GND"}),
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    #     La compuerta la prende un PC817 desde +12 V; sin señal, la 10k la deja en 0 V y la moto
    #     sigue con chispa normal (falla abierto). El zener de 15 V protege la compuerta.
    ("R28", F_R, "470", {1: "IO47", 2: "SSR_A"}),
    ("U15", F_DIP4, "PC817", {1: "SSR_A", 2: "GND", 3: "CORTE_G", 4: "+12V"}),
    ("R31", F_R, "10k", {1: "CORTE_G", 2: "GND"}),
    ("DZ1", F_D41, "1N4744 (15V)", {1: "CORTE_G", 2: "GND"}),      # 1=K
    ("Q9", F_TO220, "IRF840", {1: "CORTE_G", 2: "CORTE_D", 3: "GND"}),   # 1=G 2=D 3=S
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
    # --- Salida aislada libre (colector abierto, hasta 50 mA) <- GPIO44 (RX0: el arranque no lo mueve)
    ("R30", F_R, "470", {1: "IO44", 2: "SAL_A"}),
    ("U16", F_DIP4, "PC817", {1: "SAL_A", 2: "GND", 3: "SAL_E", 4: "SAL_C"}),
    ("J19", F_BORNE35(2), "SALIDA AISLADA", {1: "SAL_C", 2: "SAL_E"}),

    # --- 3 relevadores: 1 = bloqueo anti-robo (GPIO40), 2 (GPIO38), 3 (GPIO45). GPIO45 debe estar
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#   GPIO4            voltaje de las celdas (divisor 100k/100k, ya existía como Li-ion)
#   GPIO3, GPIO46    entradas aisladas 2 y 3 (activa = LOW, usa INPUT_PULLUP)
#   GPIO44           salida aislada libre
#   GPIO18 neutral   ahora por optoacoplador: en neutral el cable está a tierra, el LED se apaga y
#                    el pin lee HIGH  ->  NEUTRAL_ACTIVO_BAJO = false

# Rótulos de serigrafía de cada conector, en el orden de sus pines (pin 1 primero)
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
